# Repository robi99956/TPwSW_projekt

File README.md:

Wymagany dostęp do portu szeregowego, by GUI działało prawidłowo

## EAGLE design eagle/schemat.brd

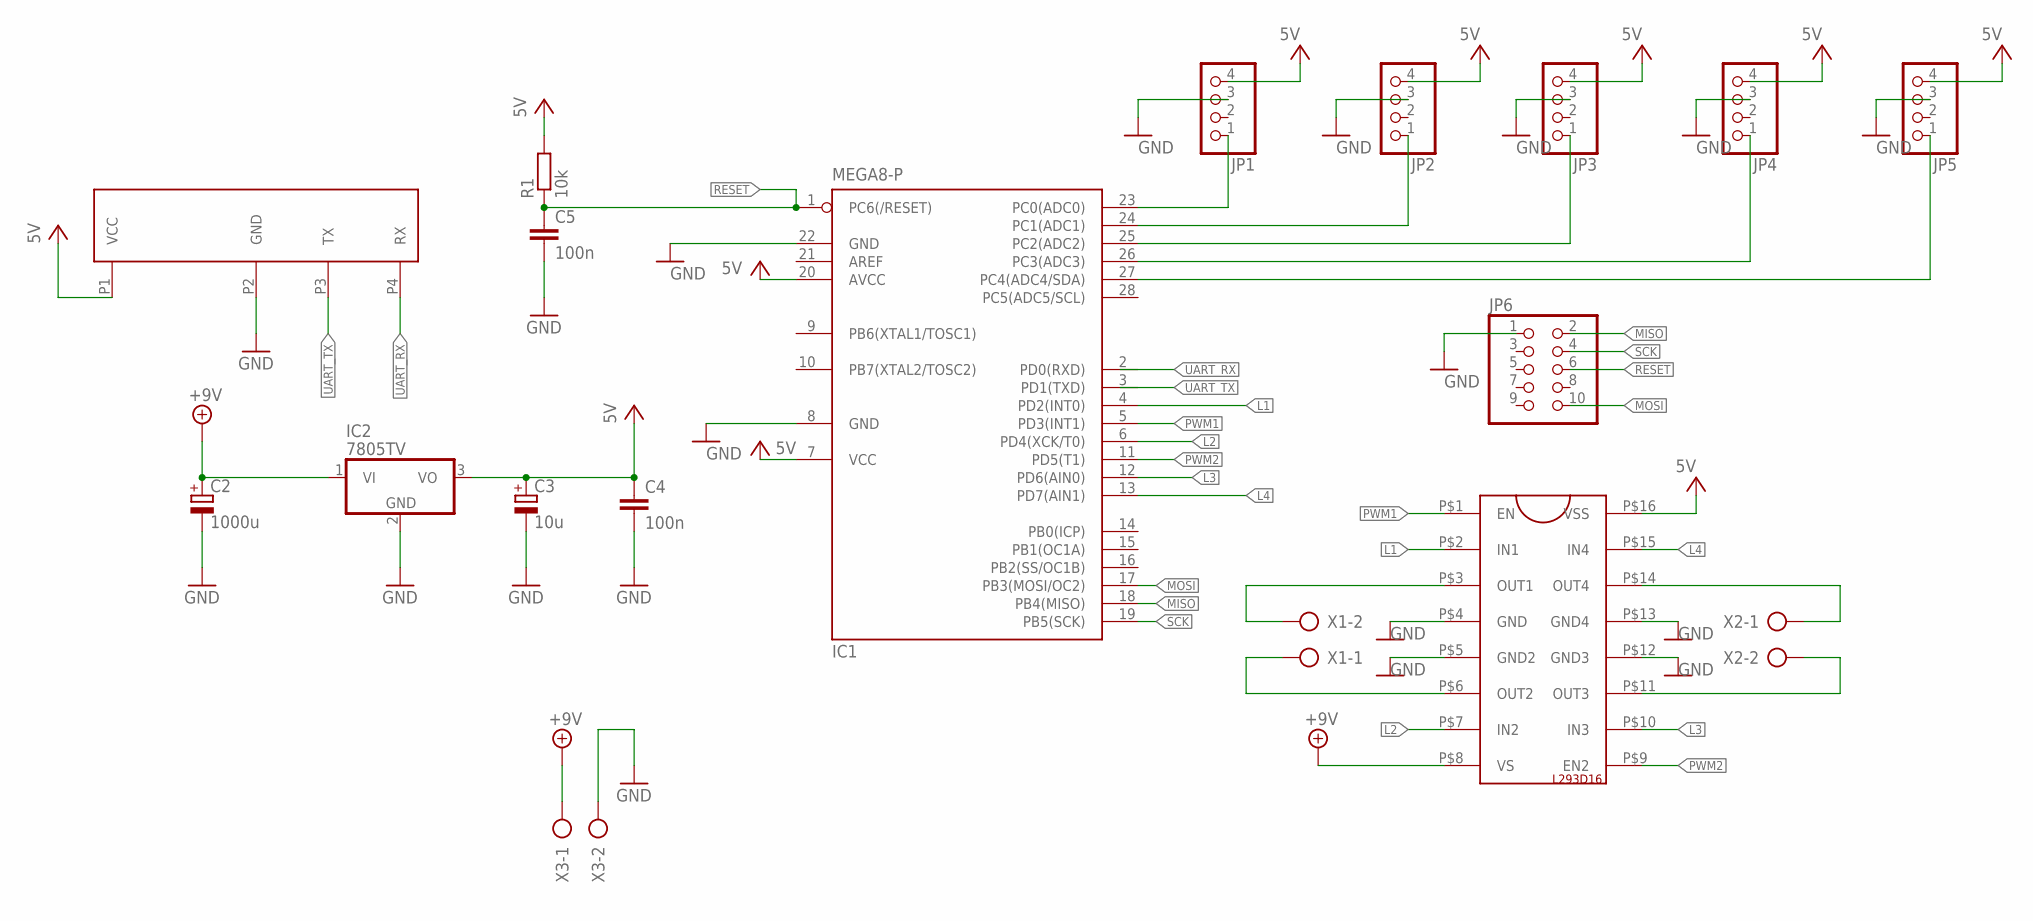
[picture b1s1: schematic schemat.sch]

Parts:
C2: 1000u; E5-10,5
C3: 10u; E5-10,5
C4, C5: 100n; C050-075X075
IC1: MEGA8-P; DIL28-3
IC2: 7805TV; TO220V
JP1, JP2, JP3, JP4, JP5: PINHD-1X4/90; 1X04/90
JP6: PINHD-2X5; 2X05
R1: 10k; 0309/10
U$1: BTM222BTM222; BTM222
U$2: L293D16L293D16; L293D
X1, X2, X3: AK500/2

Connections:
+9V: C2.+, IC2.1 (VI), U$2.P$8 (VS), X3.1
GND: C2.-, C3.-, C4.2, C5.2, IC1.8 (GND), IC1.22 (GND), IC2.2 (GND), JP1.3, JP2.3, JP3.3, JP4.3, JP5.3, JP6.1, U$1.P2 (GND), U$2.P$4 (GND), U$2.P$5 (GND2), U$2.P$12 (GND3), U$2.P$13 (GND4), X3.2
L1: IC1.4 (PD2(INT0)), U$2.P$2 (IN1)
L2: IC1.6 (PD4(XCK/T0)), U$2.P$7 (IN2)
L3: IC1.12 (PD6(AIN0)), U$2.P$10 (IN3)
L4: IC1.13 (PD7(AIN1)), U$2.P$15 (IN4)
MISO: IC1.18 (PB4(MISO)), JP6.2
MOSI: IC1.17 (PB3(MOSI/OC2)), JP6.10
unnamed: IC1.24 (PC1(ADC1)), JP2.1
unnamed: IC1.25 (PC2(ADC2)), JP3.1
unnamed: IC1.23 (PC0(ADC0)), JP1.1
unnamed: IC1.26 (PC3(ADC3)), JP4.1
unnamed: IC1.27 (PC4(ADC4/SDA)), JP5.1
unnamed: U$2.P$6 (OUT2), X1.1
unnamed: U$2.P$3 (OUT1), X1.2
unnamed: U$2.P$14 (OUT4), X2.1
unnamed: U$2.P$11 (OUT3), X2.2
PWM1: IC1.5 (PD3(INT1)), U$2.P$1 (EN)
PWM2: IC1.11 (PD5(T1)), U$2.P$9 (EN2)
RESET: C5.1, IC1.1 (PC6(/RESET)), JP6.6, R1.1
SCK: IC1.19 (PB5(SCK)), JP6.4
UART_RX: IC1.2 (PD0(RXD)), U$1.P4 (RX)
UART_TX: IC1.3 (PD1(TXD)), U$1.P3 (TX)
VCC: C3.+, C4.1, IC1.7 (VCC), IC1.20 (AVCC), IC2.3 (VO), JP1.4, JP2.4, JP3.4, JP4.4, JP5.4, R1.2, U$1.P1 (VCC), U$2.P$16 (VSS)

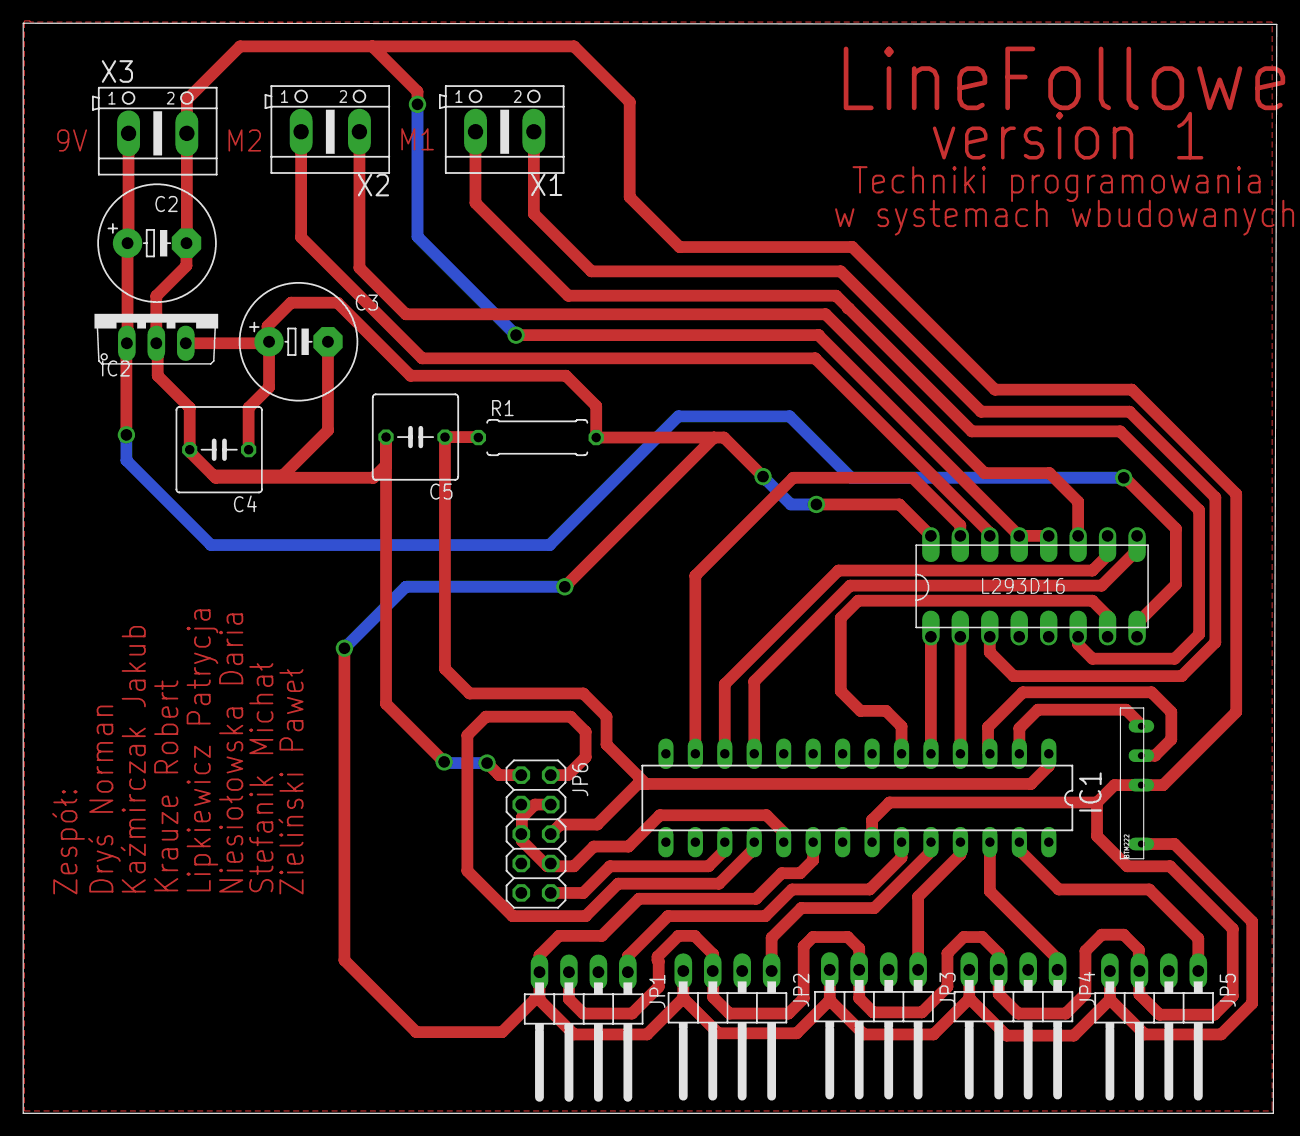
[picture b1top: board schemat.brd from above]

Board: 2 copper layers, 108.1 x 94.0 mm, 18 parts (0 on the bottom side), 24 nets.

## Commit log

2020-03-03 Dodanie pliku README
2020-04-19 added eagle files
2020-04-22 Program sprawdzający pracę silników
2020-05-17 GUI+ramka do przesyłu danych (Processing)
2020-05-17 zmiana prowadzenia ścieżek
    zmiany ścieżek, dodatnie tła do napisów, zmniejszenie wielkości płytki
